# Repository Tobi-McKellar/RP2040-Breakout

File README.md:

# RP2040-Breakout
A simple RP2040 breakout.

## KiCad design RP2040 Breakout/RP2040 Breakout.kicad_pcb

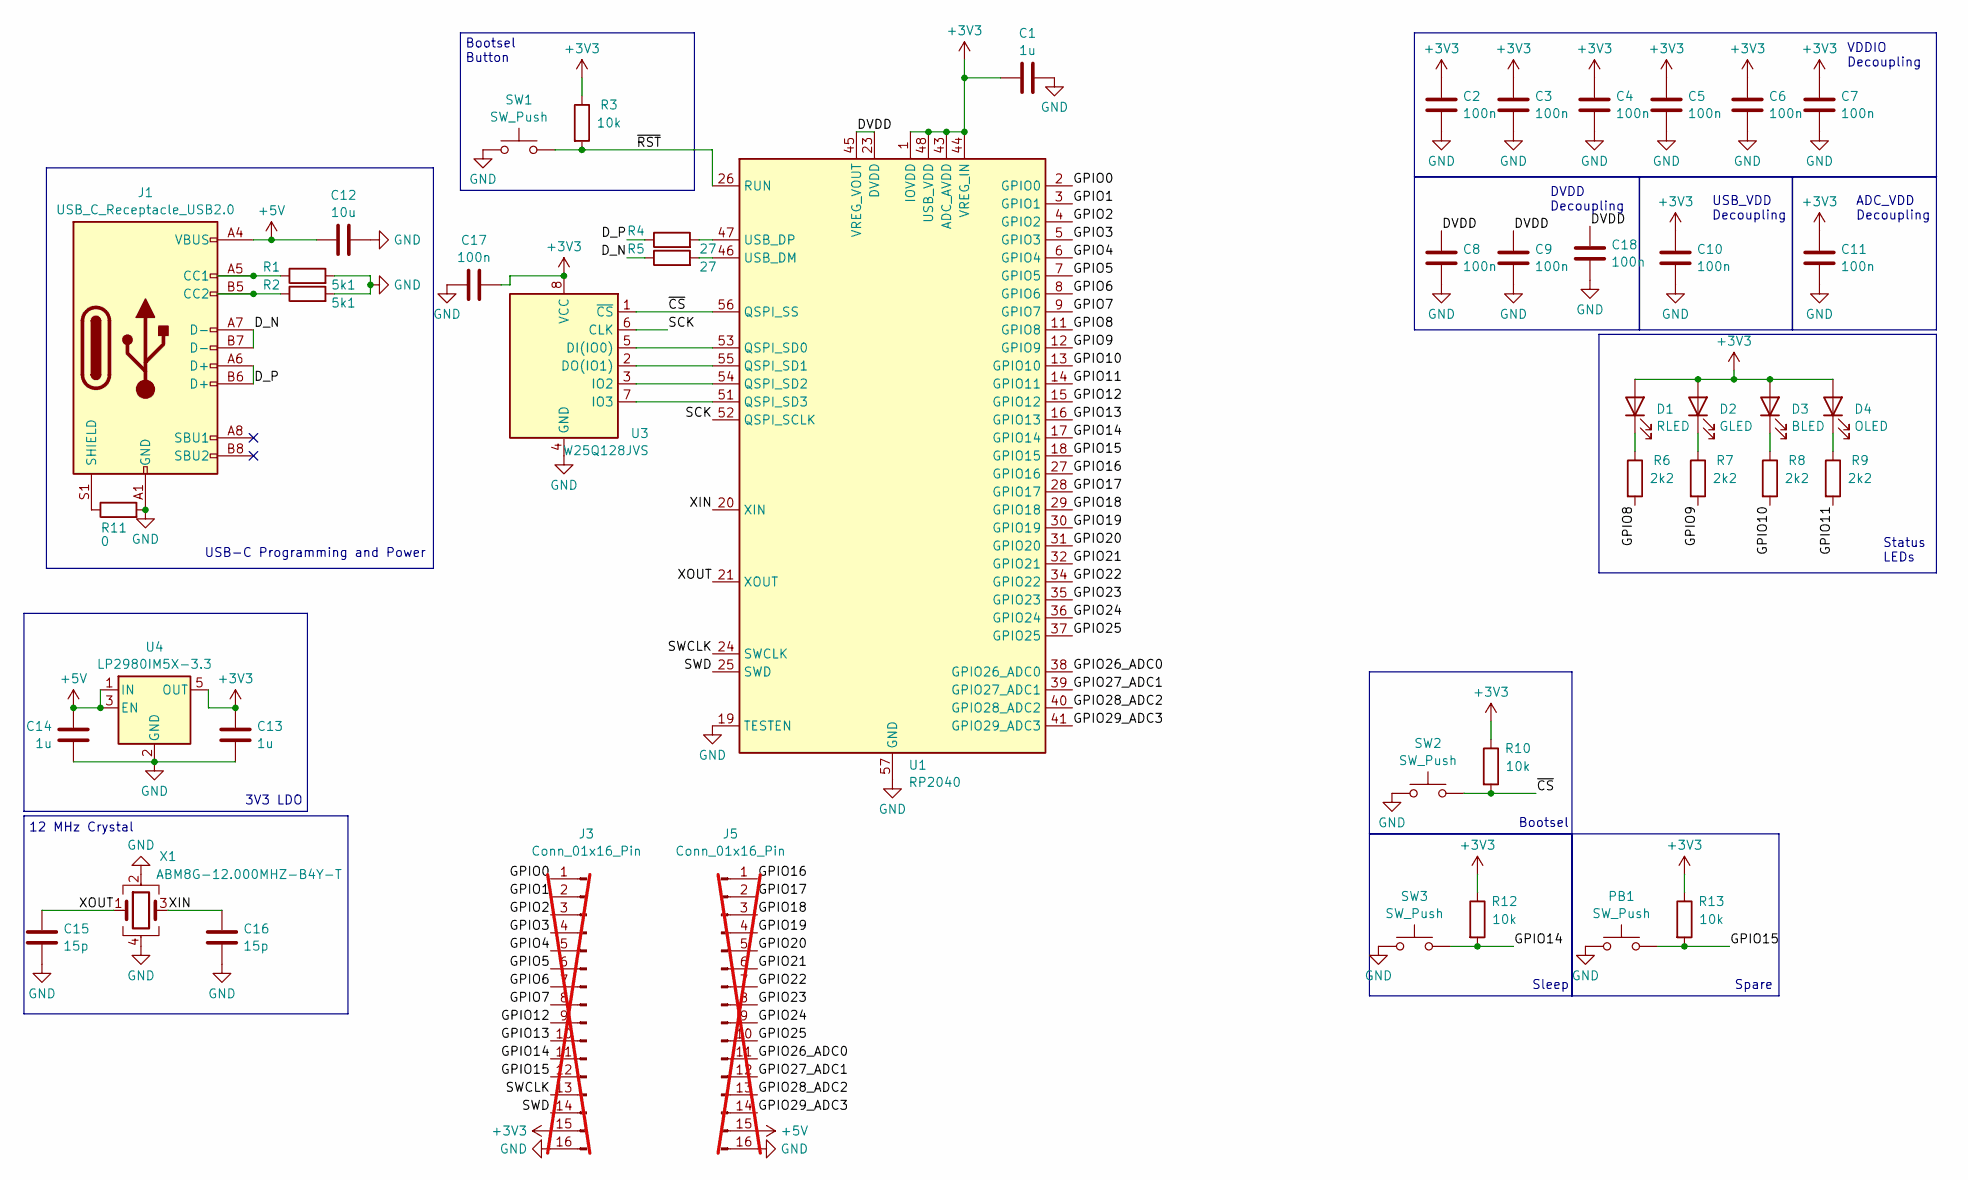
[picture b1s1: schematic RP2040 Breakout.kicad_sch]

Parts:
C1, C13, C14: 1u; C_0402_1005Metric; JLC Part Number C528974
C2, C3, C4, C5, C6, C7, C8, C9, C10, C11, C17, C18: 100n; C_0402_1005Metric; JLC Part Number C60474
C12: 10u; C_0603_1608Metric; JLC Part Number C2959727
C15, C16: 15p; C_0402_1005Metric; JLC Part Number C106997
D1: RLED; D_0402_1005Metric; JLC Part Number C264407
D2: GLED; D_0402_1005Metric; JLC Part Number C264408
D3: BLED; D_0402_1005Metric; JLC Part Number C131223
D4: OLED; D_0402_1005Metric; JLC Part Number C88330
J1: USB_C_Receptacle_USB2.0; USB_C_Receptacle_GCT_USB4105-xx-A_16P_TopMnt_Horizontal; JLC Part Number C2848971
J3, J5: Conn_01x16_Pin; PinHeader_1x16_P2.54mm_Vertical; not fitted
PB1: SW_Push; SW_SPST_PTS810; JLC Part Number C2888430
R1, R2: 5k1; R_0402_1005Metric; JLC Part Number C25905
R3, R10, R12, R13: 10k; R_0402_1005Metric; JLC Part Number C25744
R4, R5: 27; R_0402_1005Metric; JLC Part Number C25885
R6, R7, R8, R9: 2k2; R_0402_1005Metric; JLC Part Number C25879
R11: 0; R_0402_1005Metric; JLC Part Number C25885
SW1, SW2, SW3: SW_Push; SW_SPST_PTS810; JLC Part Number C2888430
U1: RP2040; QFN-56-1EP_7x7mm_P0.4mm_EP3.2x3.2mm; JLC Part Number C2040
U3: W25Q128JVS; SOIC-8_5.23x5.23mm_P1.27mm; JLC Part Number C97521
U4: LP2980IM5X-3.3; SOT-23-5; JLC Part Number C5380654
X1: ABM8G-12.000MHZ-B4Y-T; Oscillator_SMD_Abracon_ASE-4Pin_3.2x2.5mm; JLC Part Number C276421

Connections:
+3V3: C1.1, C2.2, C3.2, C4.2, C5.2, C6.2, C7.2, C10.2, C11.2, C13.2, C17.1, D1.2 (A), D2.2 (A), D3.2 (A), D4.2 (A), J3.15, R3.1, R10.1, R12.1, R13.1, U1.1 (IOVDD), U1.10 (IOVDD), U1.22 (IOVDD), U1.33 (IOVDD), U1.42 (IOVDD), U1.43 (ADC_AVDD), U1.44 (VREG_IN), U1.48 (USB_VDD), U1.49 (IOVDD), U3.8 (VCC), U4.5 (OUT)
+5V: C12.1, C14.2, J1.A4 (VBUS), J1.A9 (VBUS), J1.B4 (VBUS), J1.B9 (VBUS), J5.15, U4.1 (IN), U4.3 (EN)
/DVDD: C8.2, C9.2, C18.2, U1.23 (DVDD), U1.45 (VREG_VOUT), U1.50 (DVDD)
/D_N: J1.A7 (D-), J1.B7 (D-), R5.1
/D_P: J1.A6 (D+), J1.B6 (D+), R4.1
/GPIO0: J3.1, U1.2 (GPIO0)
/GPIO1: J3.2, U1.3 (GPIO1)
/GPIO2: J3.3, U1.4 (GPIO2)
/GPIO3: J3.4, U1.5 (GPIO3)
/GPIO4: J3.5, U1.6 (GPIO4)
/GPIO5: J3.6, U1.7 (GPIO5)
/GPIO6: J3.7, U1.8 (GPIO6)
/GPIO7: J3.8, U1.9 (GPIO7)
/GPIO8: R6.2, U1.11 (GPIO8)
/GPIO9: R7.2, U1.12 (GPIO9)
/GPIO10: R8.2, U1.13 (GPIO10)
/GPIO11: R9.2, U1.14 (GPIO11)
/GPIO12: J3.9, U1.15 (GPIO12)
/GPIO13: J3.10, U1.16 (GPIO13)
/GPIO14: J3.11, R12.2, SW3.2, U1.17 (GPIO14)
/GPIO15: J3.12, PB1.2, R13.2, U1.18 (GPIO15)
/GPIO16: J5.1, U1.27 (GPIO16)
/GPIO17: J5.2, U1.28 (GPIO17)
/GPIO18: J5.3, U1.29 (GPIO18)
/GPIO19: J5.4, U1.30 (GPIO19)
/GPIO20: J5.5, U1.31 (GPIO20)
/GPIO21: J5.6, U1.32 (GPIO21)
/GPIO22: J5.7, U1.34 (GPIO22)
/GPIO23: J5.8, U1.35 (GPIO23)
/GPIO24: J5.9, U1.36 (GPIO24)
/GPIO25: J5.10, U1.37 (GPIO25)
/GPIO26_ADC0: J5.11, U1.38 (GPIO26_ADC0)
/GPIO27_ADC1: J5.12, U1.39 (GPIO27_ADC1)
/GPIO28_ADC2: J5.13, U1.40 (GPIO28_ADC2)
/GPIO29_ADC3: J5.14, U1.41 (GPIO29_ADC3)
/SCK: U1.52 (QSPI_SCLK), U3.6 (CLK)
/SWCLK: J3.13, U1.24 (SWCLK)
/SWD: J3.14, U1.25 (SWD)
/XIN: C16.2, U1.20 (XIN), X1.3
/XOUT: C15.2, U1.21 (XOUT), X1.1
/~CS: R10.2, SW2.2, U1.56 (QSPI_SS), U3.1 (~CS)
/~RST: R3.2, SW1.2, U1.26 (RUN)
GND: C1.2, C2.1, C3.1, C4.1, C5.1, C6.1, C7.1, C8.1, C9.1, C10.1, C11.1, C12.2, C13.1, C14.1, C15.1, C16.1, C17.2, C18.1, J1.A1 (GND), J1.A12 (GND), J1.B1 (GND), J1.B12 (GND), J3.16, J5.16, PB1.1, R1.2, R2.2, R11.2, SW1.1, SW2.1, SW3.1, U1.19 (TESTEN), U1.57 (GND), U3.4 (GND), U4.2 (GND), X1.2, X1.4
unnamed: D1.1 (K), R6.1
unnamed: D2.1 (K), R7.1
unnamed: D3.1 (K), R8.1
unnamed: D4.1 (K), R9.1
unnamed: J1.A5 (CC1), R1.1
unnamed: J1.B5 (CC2), R2.1
unnamed: J1.S1 (SHIELD), R11.1
unnamed: U1.53 (QSPI_SD0), U3.5 (DI(IO0))
unnamed: U1.55 (QSPI_SD1), U3.2 (DO(IO1))
unnamed: U1.54 (QSPI_SD2), U3.3 (IO2)
unnamed: U1.51 (QSPI_SD3), U3.7 (IO3)
unnamed: R5.2, U1.46 (USB_DM)
unnamed: R4.2, U1.47 (USB_DP)

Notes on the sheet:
3V3 LDO
VDDIO Decoupling
12 MHz Crystal
Bootsel
Spare
USB-C Programming and Power
Bootsel Button
USB_VDD Decoupling
Status LEDs
Sleep
DVDD Decoupling
ADC_VDD Decoupling

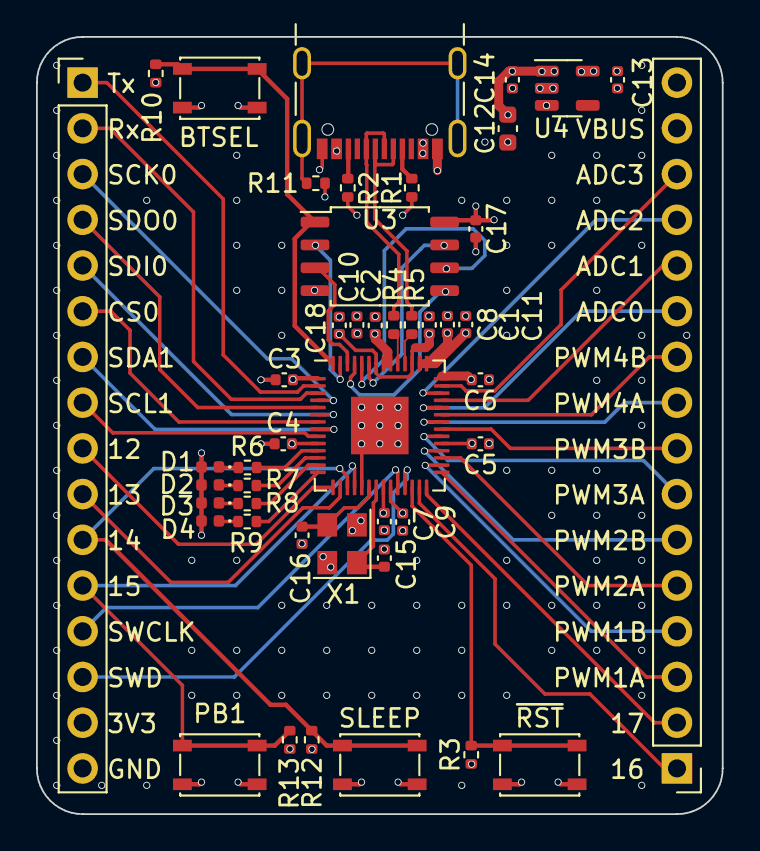
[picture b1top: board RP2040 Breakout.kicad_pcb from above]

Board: 6 copper layers, 38.1 x 43.2 mm, 47 parts (1 on the bottom side), 56 nets.

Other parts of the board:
QR*****: QRCODE_httpsgithub.comTobiMcKellarRP2040Breakout

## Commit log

2024-06-02 Add lck files to gitignore.
2024-06-02 Add kicad files.
2024-06-02 Add PCB image to readme.
2024-06-02 Cleaned up schematic a bit and rerouted buttons.
2024-06-02 Add title block to schematic.
2024-06-02 Add QR code to github page.
